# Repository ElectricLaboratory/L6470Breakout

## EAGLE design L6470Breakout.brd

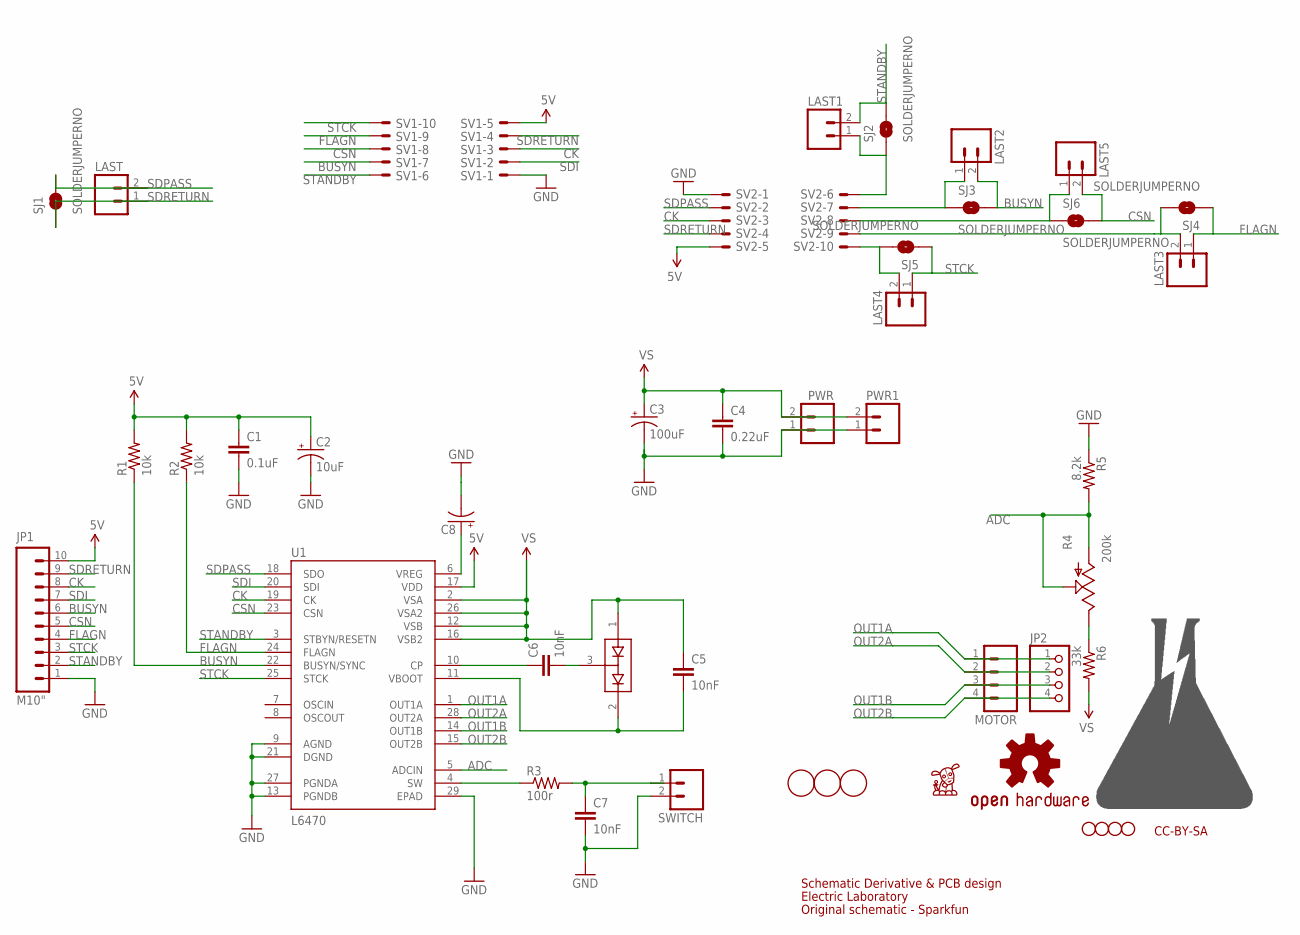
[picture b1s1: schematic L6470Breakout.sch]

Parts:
C1: 0.1uF; 0603-CAP
C2: 10uF; EIA3216
C3: 100uF; PANASONIC_E
C4: 0.22uF; 0603-CAP
C5, C6, C7: 10nF; 0603-CAP
C8: CAP_POL1206; EIA3216
D1: BAV99; SOT23
JP1: M10"; 1X10
JP2: PINHD-1X4; 1X04
JP3, JP4, JP6, JP7: STAND-OFF
LAST, LAST1, LAST2, LAST3, LAST4, LAST5: M02PTH; 1X02
MOTOR: M04SCREW; SCREWTERMINAL-3.5MM-4
PWR, PWR1: M023.5MM; SCREWTERMINAL-3.5MM-2
R1, R2: 10k; 0603-RES
R3: 100r; 0603-RES
R4: 200k; 3362U
R5: 8.2k; 0603-RES
R6: 33k; 0603-RES
SJ1, SJ2, SJ3, SJ4, SJ5, SJ6: SOLDERJUMPERNO; SJ_2S-NO
SV1, SV2: ML10E; ML10
SWITCH: M023.5MM; SCREWTERMINAL-3.5MM-2
U1: L6470; HTSSOP28
U$4: OSHW-LOGOS; OSHW-LOGO-S
U$5: EL-LOGO
U$7: TINDIE_LOGO
U$9, U$10, U$11: FIDUCIAL; FIDUCIAL_1MM

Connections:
5V: C1.1, C2.A (+), JP1.10, R1.2, R2.2, SV1.5, SV2.5, U1.17 (VDD)
ADC: R4.P$2 (S), R4.P$3 (A), R5.2, U1.5 (ADCIN)
BUSYN: JP1.6, LAST2.2, R1.1, SJ3.2, SV1.7, U1.22 (BUSYN/SYNC)
CK: JP1.8, SV1.3, SV2.3, U1.19 (CK)
CSN: JP1.5, LAST5.2, SJ6.2, SV1.8, U1.23 (CSN)
FLAGN: JP1.4, LAST3.1, R2.1, SJ4.1, SV1.9, U1.24 (FLAGN)
GND: C1.2, C2.C (-), C3.-, C4.2, C7.2, C8.C (-), JP1.1, PWR.1, PWR1.1, R5.1, SV1.1, SV2.1, SWITCH.2, U1.9 (AGND), U1.13 (PGNDB), U1.21 (DGND), U1.27 (PGNDA), U1.29 (EPAD)
unnamed: C8.A (+), U1.6 (VREG)
unnamed: LAST2.1, SJ3.1, SV2.7
unnamed: LAST5.1, SJ6.1, SV2.8
unnamed: R3.1, U1.4 (SW)
unnamed: C7.1, R3.2, SWITCH.1
unnamed: C6.1, U1.10 (CP)
unnamed: C6.2, D1.3 (COM)
unnamed: C5.2, D1.2 (C2), U1.11 (VBOOT)
unnamed: R4.P$1 (E), R6.1
unnamed: LAST3.2, SJ4.2, SV2.9
unnamed: LAST1.1, SJ2.1, SV2.6
unnamed: LAST4.2, SJ5.2, SV2.10
OUT1A: JP2.1, MOTOR.1, U1.1 (OUT1A)
OUT1B: JP2.3, MOTOR.3, U1.14 (OUT1B)
OUT2A: JP2.2, MOTOR.2, U1.28 (OUT2A)
OUT2B: JP2.4, MOTOR.4, U1.15 (OUT2B)
SDI: JP1.7, SV1.2, U1.20 (SDI)
SDPASS: LAST.2, SJ1.2, SV2.2, U1.18 (SDO)
SDRETURN: JP1.9, LAST.1, SJ1.1, SV1.4, SV2.4
STANDBY: JP1.2, LAST1.2, SJ2.2, SV1.6, U1.3 (STBYN/RESETN)
STCK: JP1.3, LAST4.1, SJ5.1, SV1.10, U1.25 (STCK)
VCC: C3.+, C4.1, C5.1, D1.1 (A1), PWR.2, PWR1.2, R6.2, U1.2 (VSA), U1.12 (VSB), U1.16 (VSB2), U1.26 (VSA2)

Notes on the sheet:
CC-BY-SA
Original schematic - Sparkfun
Schematic Derivative & PCB design
Electric Laboratory

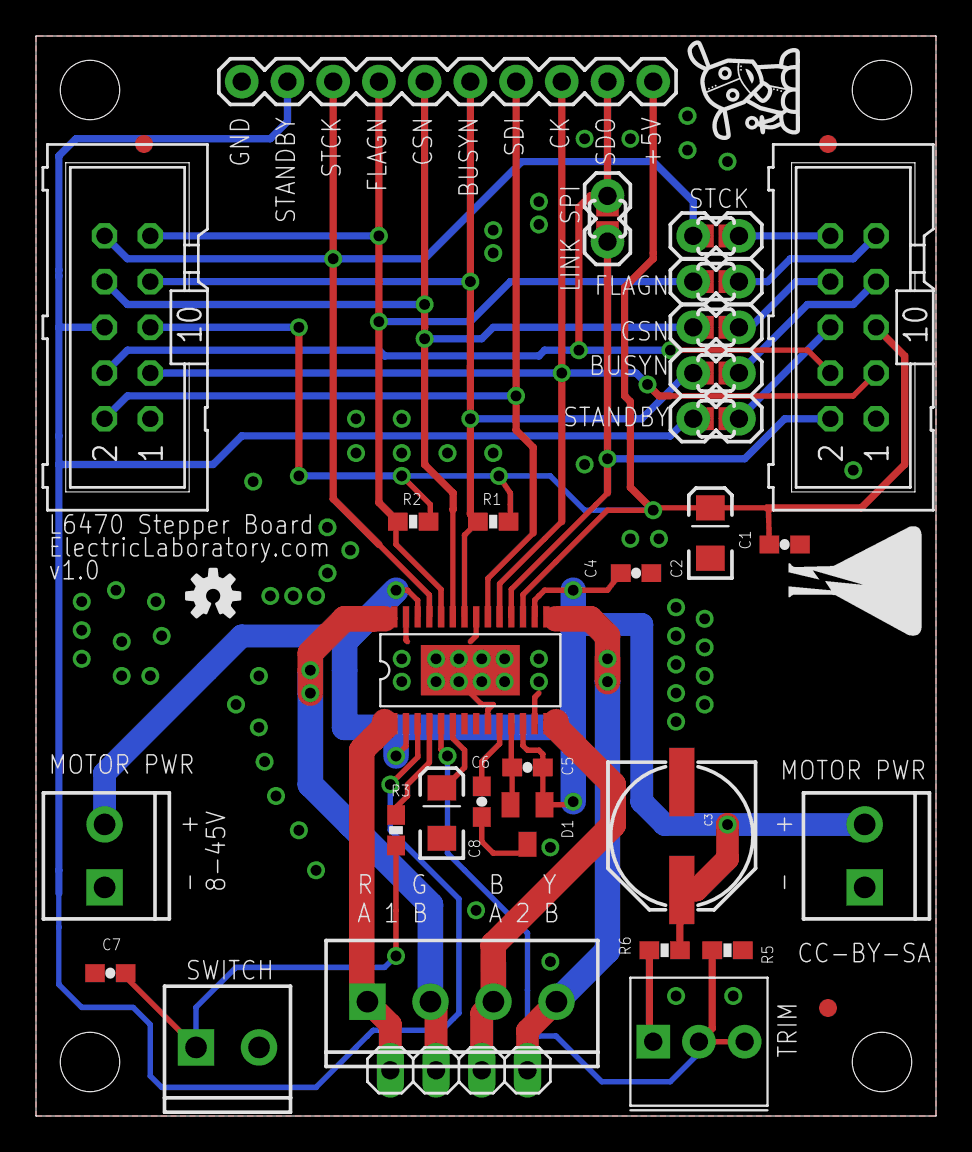
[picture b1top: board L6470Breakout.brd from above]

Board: 2 copper layers, 50.0 x 60.0 mm, 46 parts (0 on the bottom side), 29 nets.

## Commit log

2013-03-03 Production version

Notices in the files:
parts and their libraries:
SparkFun-Passives: Licensing: CC v3.0 Share-Alike You are welcome to use this library for commercial purposes.
